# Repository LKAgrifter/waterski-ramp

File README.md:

# Waterski Ramp Controller

Firmware for a motorized waterski jump ramp: a **ramp controller** that drives the lift motor, the ramp's water
pump and the height sensors, and handheld **remotes** that talk to it over LoRa radio.

Both run on the **Heltec WiFi LoRa 32 (V3)** board (ESP32-S3 + SX1262 LoRa radio + 128x64 OLED).

> Hardware files (PCB, wiring, CAD) will be added under `hardware/`. Full documentation is coming.

## What's in here

```
firmware/
  Ramp_Control/   Ramp controller sketch (open Ramp_Control.ino in the Arduino IDE)
  Ramp_Remote/    Remote sketch (open Ramp_Remote.ino in the Arduino IDE)
flasher/          Browser flasher page (published to GitHub Pages by the build)
hardware/         PCB, wiring and CAD files (to come)
docs/             USER_GUIDE.md (how to use it), DEVELOPMENT.md (how it works), ARDUINO_IDE_SETUP.md (step-by-step guide)
tests/host/       PC simulation tests (optional - see tests/host/README.md)
.github/          Automatic build: tests, compiles both sketches, publishes the flasher
```

Each sketch folder is a normal Arduino sketch: every `.ino` file in it opens as a tab and they're compiled
together. You never need anything outside the folder to build it.

## Just want to flash a board? Use the browser flasher

No software to install: open the **flasher page** in Chrome or Edge on a computer, plug in the board, click
*Install*: **https://lkagrifter.github.io/waterski-ramp/**

The page always has the latest firmware from this repo, built automatically. It never erases the board, so saved
settings and the board's Heltec radio license are kept.

## Changing the code: Arduino IDE

Full step-by-step guide with pictures: `docs/ARDUINO_IDE_SETUP.md`. The short version:

1. Install the [Arduino IDE](https://www.arduino.cc/en/software) (2.x).
2. **Add the Heltec boards:** File > Preferences > *Additional boards manager URLs*, add
   `https://resource.heltec.cn/download/package_heltec_esp32_index.json`
   then Tools > Board > Boards Manager, search **Heltec ESP32** and install it.
3. **Install the Heltec library:** Tools > Manage Libraries, search **Heltec ESP32 Dev-Boards** and install it.
   It provides `LoRaWan_APP.h` (radio) and `HT_SSD1306Wire.h` (screen). No other libraries are needed.
4. Tools > Board: **Heltec WiFi LoRa 32(V3)**. Pick the board's USB port under Tools > Port.
5. Open `firmware/Ramp_Control/Ramp_Control.ino` (ramp) or `firmware/Ramp_Remote/Ramp_Remote.ino` (remote)
   and click **Upload**.

Versions known to work: *(fill in: Arduino IDE x.y, Heltec ESP32 board package x.y.z, Heltec ESP32 Dev-Boards x.y.z)*

**Flash the ramp and the remotes from the same version of this repo.** They share a radio message format.

## Making another remote

Up to **4 remotes** can talk to one ramp.

1. Build the remote hardware (same board and buttons as the existing remote).
2. Flash it with the browser flasher (or the Arduino IDE). Every remote uses the same firmware.
3. On the new remote, hold MENU to reach the **NETWORK** page, then **hold UP + DOWN together for 2 seconds** to change its ID
   (1 -> 2 -> 3 -> 4). Pick one no other remote uses. It's saved, and kept when you reflash.
4. It shows up on the ramp's NETWORK page.
5. Pick its **water mode**: on the WATER page, **hold UP + DOWN together for 2 seconds** to switch (the page title
   shows WATER (BOAT) or WATER (TIMER)). Also saved and kept when you reflash.
   - **BOAT** (default): for a remote that stays switched on while it's in use. BACK toggles the water; it stays
     on only while this remote is on and in range, and stops within an hour after that.
   - **TIMER**: for a remote that sleeps between presses (e.g. a solar shore remote). BACK sets a timer the same
     way as at the ramp: each tap adds 1 hour (up to 12), the tap after 12 h turns it off, hold BACK 1 s = off.

The radio settings (frequency 915 MHz, SF8, 125 kHz, coding rate 4/6) must match on every unit. They're at the
top of both main sketches. 915 MHz is for North America; Europe uses 868 MHz.

## Using it (quick version)

Full instructions for the ramp controller and the remotes, with screenshots of every page: **[docs/USER_GUIDE.md](docs/USER_GUIDE.md)**.

Hold **MENU** to step through the pages: HOME, WATER, SET HEIGHT, MANUAL, DIAGNOSTICS, NETWORK.
HOME only shows status. Heights can only be set on the **SET HEIGHT** page, so a bumped button can't move the
ramp. See `docs/DEVELOPMENT.md` for the full behaviour, safety logic and settings.

## Safety

This controls a large motorized structure. The firmware has several layers of protection (calibration lockout,
per-step motor timeout, sensor fault detection, a manual dead-man on the remote), but **firmware is not a
substitute for hardware safety**: fit a fuse or motor
thermal cutout, and a way to kill power at the ramp.

## License

To be decided.

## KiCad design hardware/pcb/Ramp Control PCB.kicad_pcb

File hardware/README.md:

# Hardware

```
hardware/
  pcb/                              KiCad project for the ramp control board
    Ramp Control PCB.kicad_pro        open this in KiCad (KiCad 10, stock libraries only)
    Ramp Control PCB.kicad_sch        schematic
    Ramp Control PCB.kicad_pcb        board layout
    Ramp Control PCB.csv              BOM (exported from the schematic)
    gerbers/                          fabrication outputs; Gerbers.zip is the fab-house upload
  cad/
    Ramp Control PCB.step             3D model of the assembled board
    Ramp Control PCB Controller Mount.SLDASM   SolidWorks assembly for the board mount
```

Notes:

- The Gerbers were exported on 2026-11-12. If the board is changed, re-export them from
  KiCad (File > Fabrication Outputs) into `pcb/gerbers/` and rebuild `Gerbers.zip`.
- The SolidWorks assembly references part files (`.SLDPRT`) that are not in the repo yet; add them to `cad/`
  so the assembly opens.
- KiCad's per-user settings (`*.kicad_prl`) and local history (`.history/`) are not tracked.

The pin assignments and wiring facts the firmware depends on are listed in `docs/DEVELOPMENT.md`
("Hardware facts the code depends on").

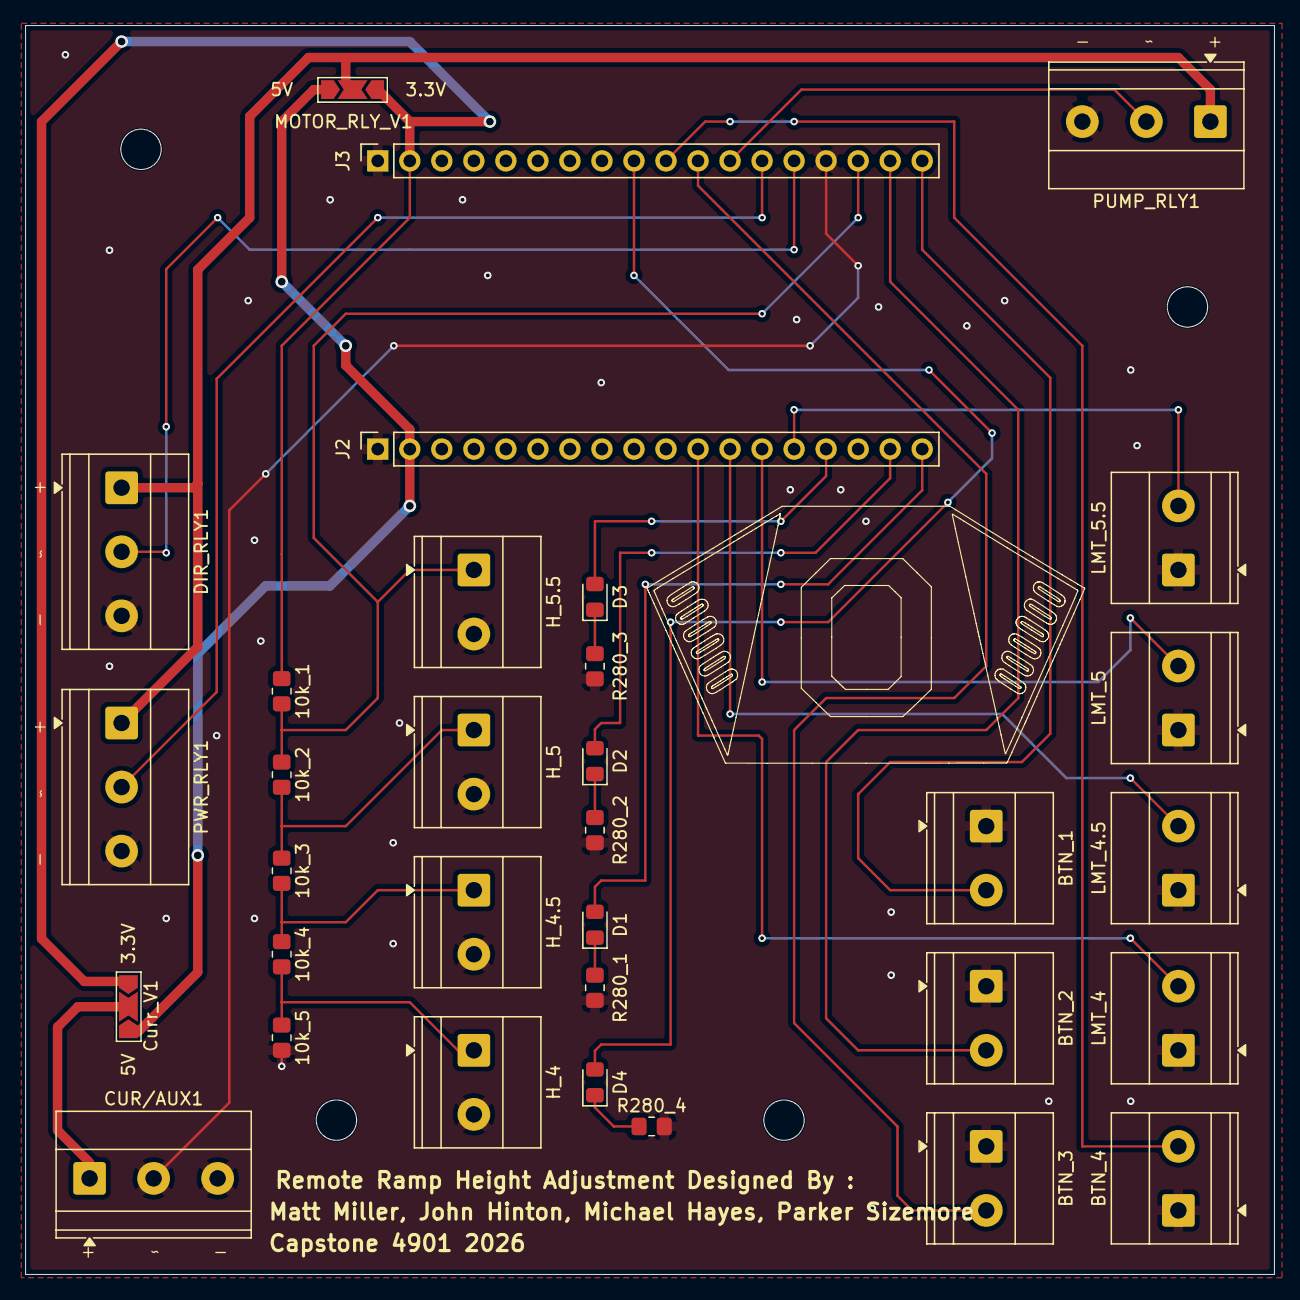
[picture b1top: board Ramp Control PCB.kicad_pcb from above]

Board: 2 copper layers, 99.1 x 99.1 mm, 33 parts (0 on the bottom side), 28 nets.

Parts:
10k_1, 10k_2, 10k_3, 10k_4, 10k_5: 10k; R_0805_2012Metric_Pad1.20x1.40mm_HandSolder
BTN_1, BTN_2, BTN_3, BTN_4: SW_Push; TerminalBlock_Phoenix_MKDS-1,5-2-5.08_1x02_P5.08mm_Horizont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
CUR/AUX1: ACS781xLRTR-050B; TerminalBlock_Phoenix_MKDS-1,5-3-5.08_1x03_P5.08mm_Horizont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
Curr_V1: SolderJumper_3_Open; SolderJumper-3_P2.0mm_Open_TrianglePad1.0x1.5mm_NumberLabels
D1, D2, D3, D4: LED; LED_0805_2012Metric_Pad1.15x1.40mm_HandSolder
DIR_RLY1: TerminalBlock_Phoenix_MKDS-1,5-3-5.08_1x03_P5.08mm_Horizont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
H_4, H_4.5, H_5, H_5.5: SW_Push; TerminalBlock_Phoenix_MKDS-1,5-2-5.08_1x02_P5.08mm_Horizont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
J2, J3: PinSocket_1x18_P2.54mm_Vertical
LMT_4, LMT_4.5, LMT_5, LMT_5.5: SW_Push_SPDT; TerminalBlock_Phoenix_MKDS-1,5-2-5.08_1x02_P5.08mm_Horizont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
MOTOR_RLY_V1: SolderJumper_3_Open; SolderJumper-3_P2.0mm_Open_TrianglePad1.0x1.5mm_NumberLabels
PUMP_RLY1: TerminalBlock_Phoenix_MKDS-1,5-3-5.08_1x03_P5.08mm_Horizont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
PWR_RLY1: TerminalBlock_Phoenix_MKDS-1,5-3-5.08_1x03_P5.08mm_Horizont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
R280_1, R280_2, R280_3, R280_4: 280; R_0805_2012Metric_Pad1.20x1.40mm_HandSolder

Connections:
/3V3: 10k_1.1, Curr_V1.1 (A), J3.2 (3V3), MOTOR_RLY_V1.1 (A)
/5V: Curr_V1.3 (B), J2.2 (5V), MOTOR_RLY_V1.3 (B)
/AUX1-VCC): CUR/AUX1.1 (VCC), Curr_V1.2 (C)
/Net-(DIR_RLY1-IN): DIR_RLY1.2 (IN), J3.14 (GPIO3)
/Net-(J3-GPIO1): J3.12 (GPIO1), PUMP_RLY1.2 (IN)
/RLY POWER: DIR_RLY1.1 (VCC), MOTOR_RLY_V1.2 (C), PUMP_RLY1.1 (VCC), PWR_RLY1.1 (VCC)
GND: 10k_5.2, BTN_1.1, BTN_2.1, BTN_3.1, BTN_4.1, CUR/AUX1.2 (GND), CUR/AUX1.3 (VOUT), DIR_RLY1.3 (GND), H_4.2, H_4.5.2, H_5.2, H_5.5.2, J2.1 (GND), J3.1 (GND), J3.15 (GPIO4), LMT_4.1 (A), LMT_4.5.1 (A), LMT_5.1 (A), LMT_5.5.1 (A), PUMP_RLY1.3 (GND), PWR_RLY1.3 (GND), R280_1.2, R280_2.2, R280_3.2, R280_4.2
unnamed: 10k_2.2, 10k_3.1, H_5.1
unnamed: 10k_3.2, 10k_4.1, H_4.5.1
unnamed: 10k_4.2, 10k_5.1, H_4.1
unnamed: D1.2 (A), J2.18 (GPIO19)
unnamed: D1.1 (K), R280_1.1
unnamed: D2.2 (A), J2.17 (GPIO20)
unnamed: D2.1 (K), R280_2.1
unnamed: D3.2 (A), J2.15 (GPIO26)
unnamed: D3.1 (K), R280_3.1
unnamed: D4.2 (A), J3.9 (GPIO40)
unnamed: D4.1 (K), R280_4.1
unnamed: J2.12 (GPIO33), LMT_4.5.2 (B)
unnamed: J2.11 (GPIO34), LMT_4.2 (B)
unnamed: J2.13 (GPIO47), LMT_5.2 (B)
unnamed: J2.14 (GPIO48), LMT_5.5.2 (B)
unnamed: J3.13 (GPIO2), PWR_RLY1.2 (IN)
unnamed: 10k_1.2, 10k_2.1, H_5.5.1, J3.16 (GPIO5)
unnamed: BTN_2.2, J3.17 (GPIO6)
unnamed: BTN_1.2, J3.18 (GPIO7)
unnamed: BTN_3.2, J3.11 (GPIO38)
unnamed: BTN_4.2, J3.10 (GPIO39)
